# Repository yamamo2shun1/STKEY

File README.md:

# STKEY

C4NDY STK をベースにした、ジョイスティック付きキーボードの新プロジェクト。

## コンセプト

- キー配列は STK と同じ横10列 × 縦4行のオーソリニア
- ジョイスティックをメイン基板から分離し、親指の自然な向きに合わせて、手前＋中央方向へ傾けて設置する
- 中央にロータリーエンコーダーを 2×2 ブロックで4個搭載
- USB HID + MIDI の複合デバイス（オーディオ機能は搭載しない）
- MCU は STM32G491、ファームウェアは TinyUSB ベース。キーマップの書き換えは Confiseur で行う想定

## ドキュメント

- [仕様整理 v0.1](docs/spec-v0.1.md) — 決定事項と未決定事項の集約
- [回路設計スタートメモ](docs/circuit-design-start.md) — 現行STKのピン割り当てと新仕様での設計開始点

## ベースプロジェクト

- [C4NDY](https://github.com/yamamo2shun1/C4NDY) — STK / KeyVLM（STM32G491 + TinyUSB、USB Audio + HID）

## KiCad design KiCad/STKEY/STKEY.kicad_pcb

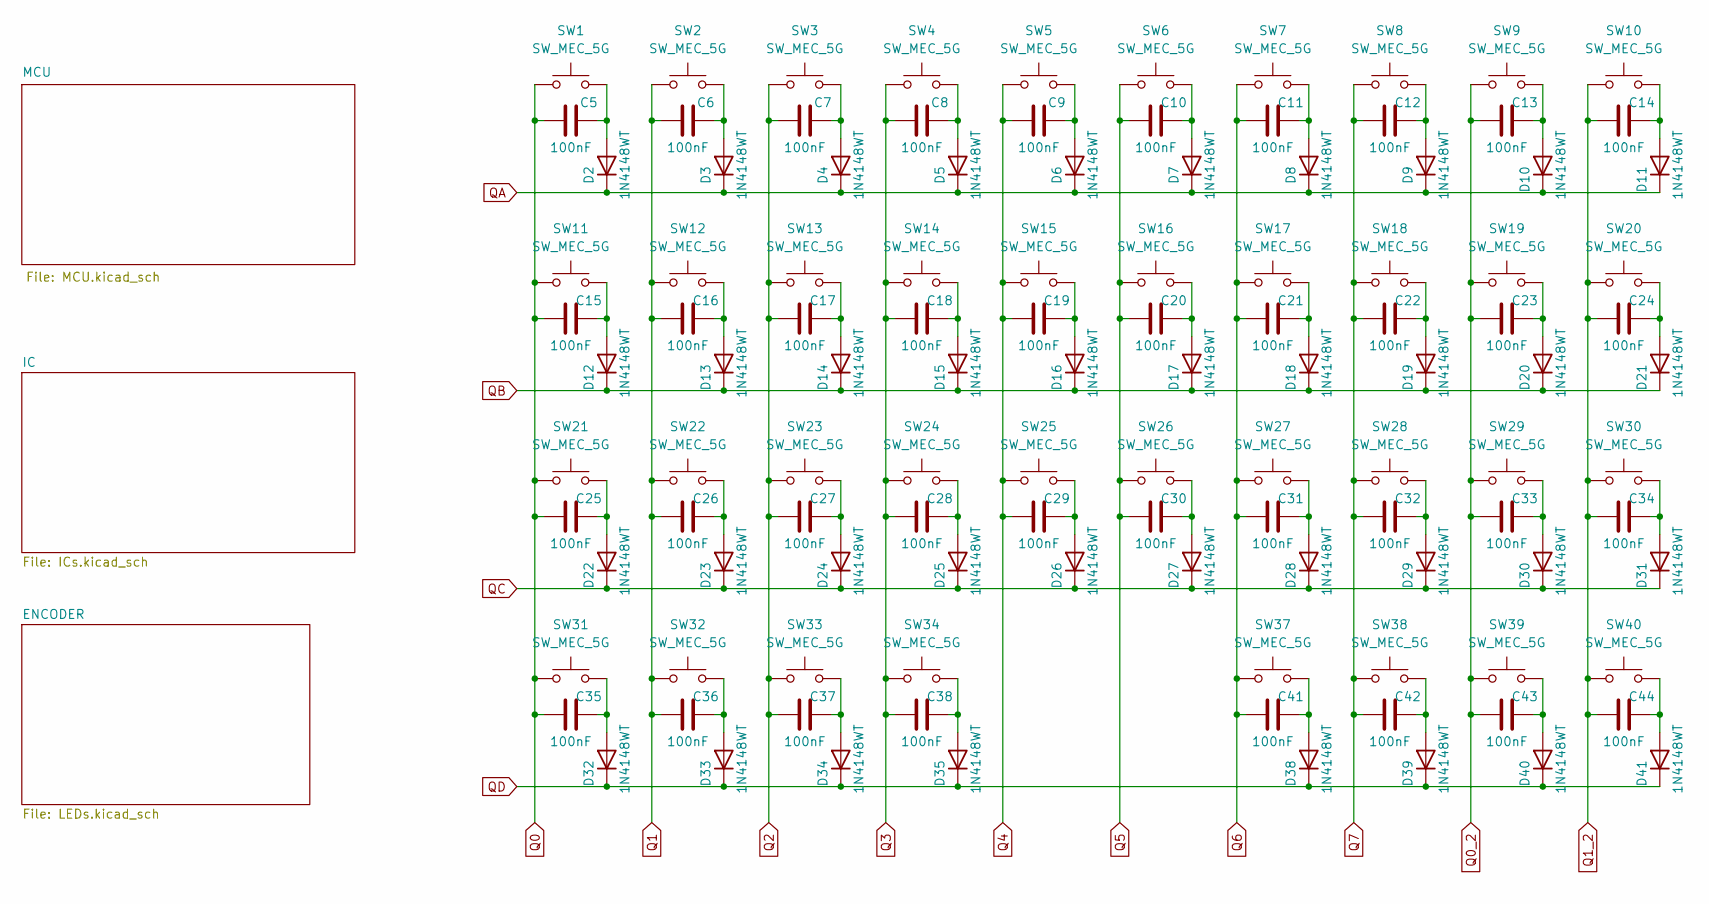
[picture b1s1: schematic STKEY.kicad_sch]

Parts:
C5, C6, C7, C8, C9, C10, C11, C12, C13, C14, C15, C16, C17, C18, C19, C20, C21, C22, C23, C24, C25, C26, C27, C28, C29, C30, C31, C32, C33, C34, C35, C36, C37, C38, C41, C42, C43, C44: 100nF; C_0402_1005Metric
D2, D3, D4, D5, D6, D7, D8, D9, D10, D11, D12, D13, D14, D15, D16, D17, D18, D19, D20, D21, D22, D23, D24, D25, D26, D27, D28, D29, D30, D31, D32, D33, D34, D35, D38, D39, D40, D41: 1N4148WT; D_SOD-523
SW1, SW2, SW3, SW4, SW5, SW6, SW7, SW8, SW9, SW10, SW11, SW12, SW13, SW14, SW15, SW16, SW17, SW18, SW19, SW20, SW21, SW22, SW23, SW24, SW25, SW26, SW27, SW28, SW29, SW30, SW31, SW32, SW33, SW34, SW37, SW38, SW39, SW40: SW_MEC_5G; Gateron_KS-27

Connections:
unnamed: C5.2, D2.2 (A), SW1.3 (B)
unnamed: C6.2, D3.2 (A), SW2.3 (B)
unnamed: C7.2, D4.2 (A), SW3.3 (B)
unnamed: C8.2, D5.2 (A), SW4.3 (B)
unnamed: C9.2, D6.2 (A), SW5.3 (B)
unnamed: C10.2, D7.2 (A), SW6.3 (B)
unnamed: C11.2, D8.2 (A), SW7.3 (B)
unnamed: C12.2, D9.2 (A), SW8.3 (B)
unnamed: C13.2, D10.2 (A), SW9.3 (B)
unnamed: C14.2, D11.2 (A), SW10.3 (B)
unnamed: C15.2, D12.2 (A), SW11.3 (B)
unnamed: C16.2, D13.2 (A), SW12.3 (B)
unnamed: C17.2, D14.2 (A), SW13.3 (B)
unnamed: C18.2, D15.2 (A), SW14.3 (B)
unnamed: C19.2, D16.2 (A), SW15.3 (B)
unnamed: C20.2, D17.2 (A), SW16.3 (B)
unnamed: C21.2, D18.2 (A), SW17.3 (B)
unnamed: C22.2, D19.2 (A), SW18.3 (B)
unnamed: C23.2, D20.2 (A), SW19.3 (B)
unnamed: C24.2, D21.2 (A), SW20.3 (B)
unnamed: C25.2, D22.2 (A), SW21.3 (B)
unnamed: C26.2, D23.2 (A), SW22.3 (B)
unnamed: C27.2, D24.2 (A), SW23.3 (B)
unnamed: C28.2, D25.2 (A), SW24.3 (B)
unnamed: C29.2, D26.2 (A), SW25.3 (B)
unnamed: C30.2, D27.2 (A), SW26.3 (B)
unnamed: C31.2, D28.2 (A), SW27.3 (B)
unnamed: C32.2, D29.2 (A), SW28.3 (B)
unnamed: C33.2, D30.2 (A), SW29.3 (B)
unnamed: C34.2, D31.2 (A), SW30.3 (B)
unnamed: C35.2, D32.2 (A), SW31.3 (B)
unnamed: C36.2, D33.2 (A), SW32.3 (B)
unnamed: C37.2, D34.2 (A), SW33.3 (B)
unnamed: C38.2, D35.2 (A), SW34.3 (B)
unnamed: C41.2, D38.2 (A), SW37.3 (B)
unnamed: C42.2, D39.2 (A), SW38.3 (B)
unnamed: C43.2, D40.2 (A), SW39.3 (B)
unnamed: C44.2, D41.2 (A), SW40.3 (B)
Q0: C5.1, C15.1, C25.1, C35.1, SW1.1 (A), SW11.1 (A), SW21.1 (A), SW31.1 (A); also elsewhere on the board
Q0_2: C13.1, C23.1, C33.1, C43.1, SW9.1 (A), SW19.1 (A), SW29.1 (A), SW39.1 (A); also elsewhere on the board
Q1: C6.1, C16.1, C26.1, C36.1, SW2.1 (A), SW12.1 (A), SW22.1 (A), SW32.1 (A); also elsewhere on the board
Q1_2: C14.1, C24.1, C34.1, C44.1, SW10.1 (A), SW20.1 (A), SW30.1 (A), SW40.1 (A); also elsewhere on the board
Q2: C7.1, C17.1, C27.1, C37.1, SW3.1 (A), SW13.1 (A), SW23.1 (A), SW33.1 (A); also elsewhere on the board
Q3: C8.1, C18.1, C28.1, C38.1, SW4.1 (A), SW14.1 (A), SW24.1 (A), SW34.1 (A); also elsewhere on the board
Q4: C9.1, C19.1, C29.1, SW5.1 (A), SW15.1 (A), SW25.1 (A); also elsewhere on the board
Q5: C10.1, C20.1, C30.1, SW6.1 (A), SW16.1 (A), SW26.1 (A); also elsewhere on the board
Q6: C11.1, C21.1, C31.1, C41.1, SW7.1 (A), SW17.1 (A), SW27.1 (A), SW37.1 (A); also elsewhere on the board
Q7: C12.1, C22.1, C32.1, C42.1, SW8.1 (A), SW18.1 (A), SW28.1 (A), SW38.1 (A); also elsewhere on the board
QA: D2.1 (K), D3.1 (K), D4.1 (K), D5.1 (K), D6.1 (K), D7.1 (K), D8.1 (K), D9.1 (K), D10.1 (K), D11.1 (K); also elsewhere on the board
QB: D12.1 (K), D13.1 (K), D14.1 (K), D15.1 (K), D16.1 (K), D17.1 (K), D18.1 (K), D19.1 (K), D20.1 (K), D21.1 (K); also elsewhere on the board
QC: D22.1 (K), D23.1 (K), D24.1 (K), D25.1 (K), D26.1 (K), D27.1 (K), D28.1 (K), D29.1 (K), D30.1 (K), D31.1 (K); also elsewhere on the board
QD: D32.1 (K), D33.1 (K), D34.1 (K), D35.1 (K), D38.1 (K), D39.1 (K), D40.1 (K), D41.1 (K); also elsewhere on the board

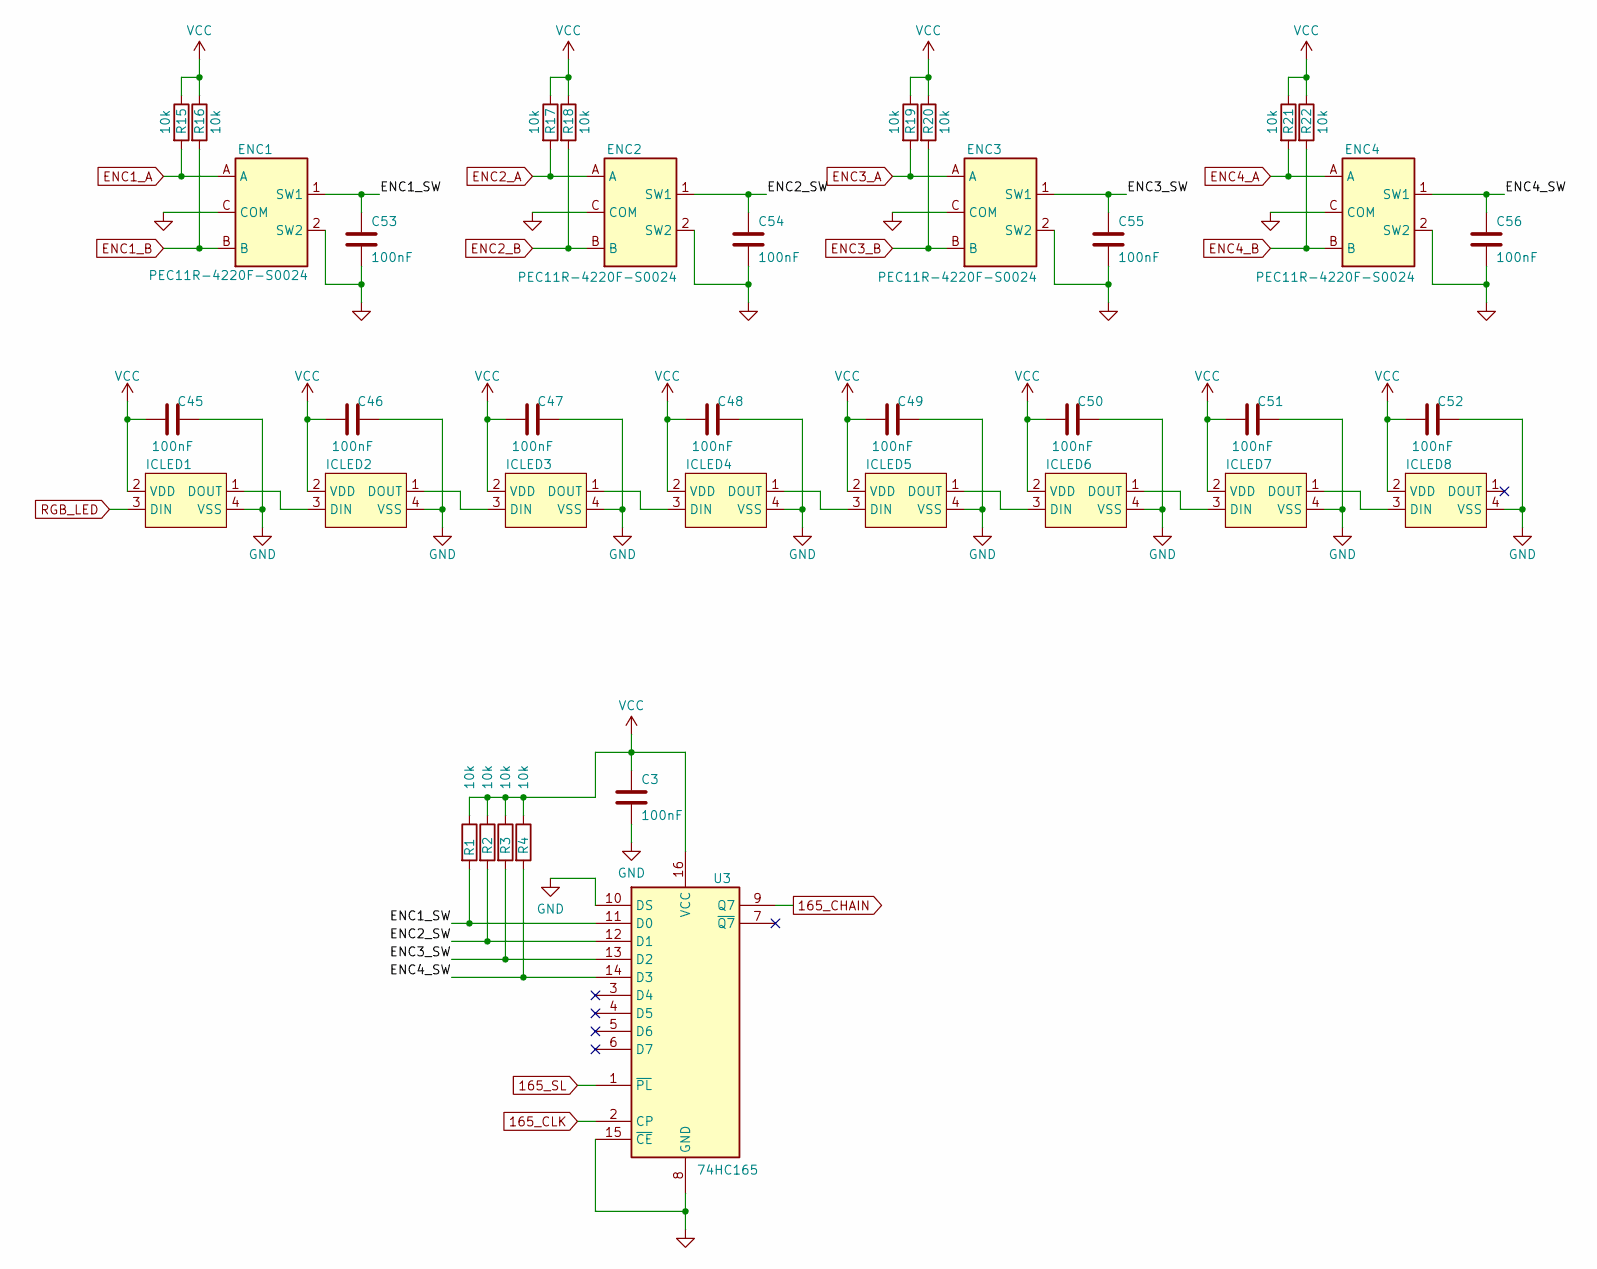
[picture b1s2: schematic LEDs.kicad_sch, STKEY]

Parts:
C3, C45, C46, C47, C48, C49, C50, C51, C52, C53, C54, C55, C56: 100nF; C_0402_1005Metric
ENC1, ENC2, ENC3, ENC4: PEC11R-4220F-S0024; XDCR_PEC11R-4220F-S0024
ICLED1, ICLED2, ICLED3, ICLED4, ICLED5, ICLED6, ICLED7, ICLED8: 1312020030000
R1, R2, R3, R4, R15, R16, R17, R18, R19, R20, R21, R22: 10k; R_0402_1005Metric
U3: 74HC165; SOIC-16_3.9x9.9mm_P1.27mm

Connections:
165_CHAIN: U3.9 (Q7); also elsewhere on the board
165_CLK: U3.2 (CP); also elsewhere on the board
165_SL: U3.1 (~PL); also elsewhere on the board
/ENCODER/ENC1_SW: C53.1, ENC1.1 (SW1), R1.2, U3.11 (D0)
/ENCODER/ENC2_SW: C54.1, ENC2.1 (SW1), R2.2, U3.12 (D1)
/ENCODER/ENC3_SW: C55.1, ENC3.1 (SW1), R3.2, U3.13 (D2)
/ENCODER/ENC4_SW: C56.1, ENC4.1 (SW1), R4.2, U3.14 (D3)
ENC1_A: ENC1.A, R15.2; also elsewhere on the board
ENC1_B: ENC1.B, R16.2; also elsewhere on the board
ENC2_A: ENC2.A, R17.2; also elsewhere on the board
ENC2_B: ENC2.B, R18.2; also elsewhere on the board
ENC3_A: ENC3.A, R19.2; also elsewhere on the board
ENC3_B: ENC3.B, R20.2; also elsewhere on the board
ENC4_A: ENC4.A, R21.2; also elsewhere on the board
ENC4_B: ENC4.B, R22.2; also elsewhere on the board
GND: C3.2, C45.2, C46.2, C47.2, C48.2, C49.2, C50.2, C51.2, C52.2, C53.2, C54.2, C55.2, C56.2, ENC1.2 (SW2), ENC1.C (COM), ENC2.2 (SW2), ENC2.C (COM), ENC3.2 (SW2), ENC3.C (COM), ENC4.2 (SW2), ENC4.C (COM), ICLED1.4 (VSS), ICLED2.4 (VSS), ICLED3.4 (VSS), ICLED4.4 (VSS), ICLED5.4 (VSS), ICLED6.4 (VSS), ICLED7.4 (VSS), ICLED8.4 (VSS), U3.8 (GND), U3.10 (DS), U3.15 (~CE); also elsewhere on the board
unnamed: ICLED1.1 (DOUT), ICLED2.3 (DIN)
unnamed: ICLED2.1 (DOUT), ICLED3.3 (DIN)
unnamed: ICLED3.1 (DOUT), ICLED4.3 (DIN)
unnamed: ICLED4.1 (DOUT), ICLED5.3 (DIN)
unnamed: ICLED5.1 (DOUT), ICLED6.3 (DIN)
unnamed: ICLED6.1 (DOUT), ICLED7.3 (DIN)
unnamed: ICLED7.1 (DOUT), ICLED8.3 (DIN)
RGB_LED: ICLED1.3 (DIN); also elsewhere on the board
VCC: C3.1, C45.1, C46.1, C47.1, C48.1, C49.1, C50.1, C51.1, C52.1, ICLED1.2 (VDD), ICLED2.2 (VDD), ICLED3.2 (VDD), ICLED4.2 (VDD), ICLED5.2 (VDD), ICLED6.2 (VDD), ICLED7.2 (VDD), ICLED8.2 (VDD), R1.1, R2.1, R3.1, R4.1, R15.1, R16.1, R17.1, R18.1, R19.1, R20.1, R21.1, R22.1, U3.16 (VCC); also elsewhere on the board

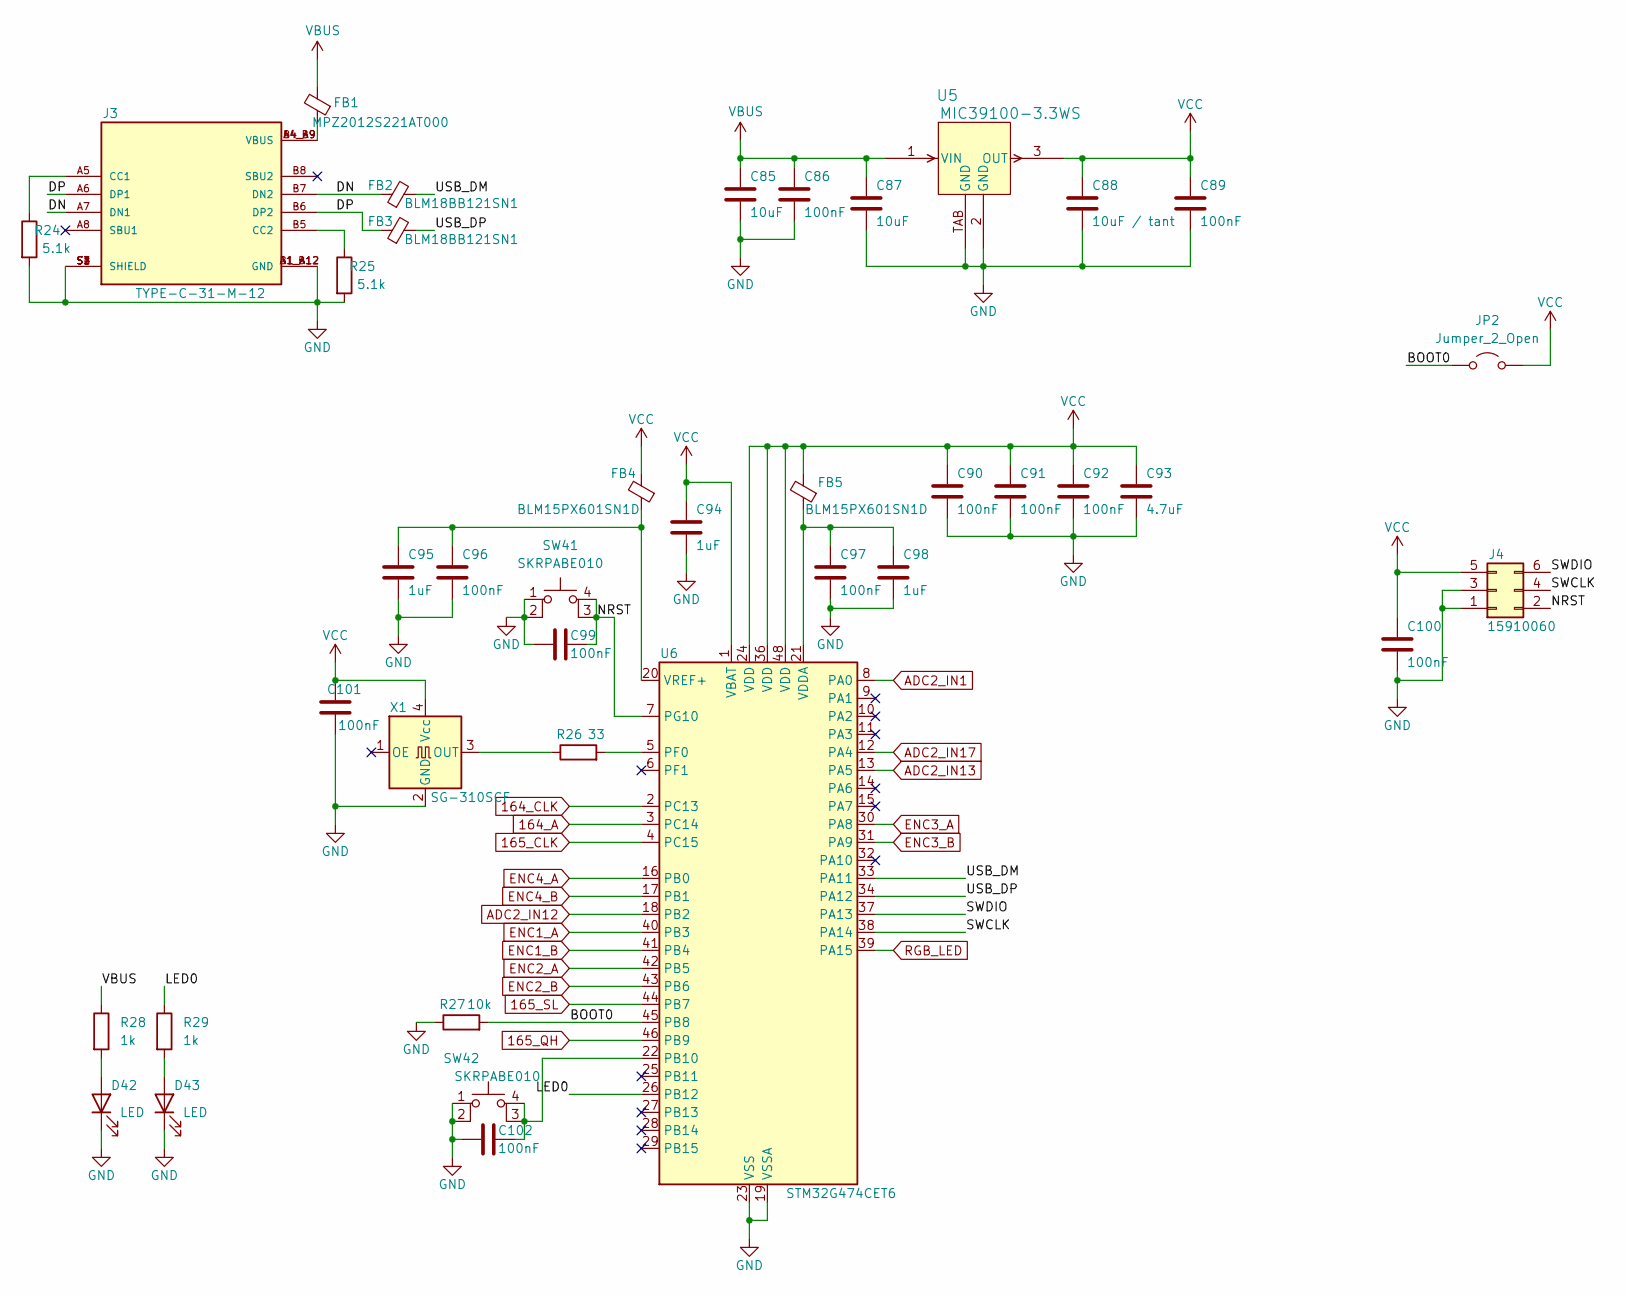
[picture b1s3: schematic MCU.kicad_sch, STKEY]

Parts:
C85, C87: 10uF; C_0603_1608Metric
C86, C89: 100nF; C_0603_1608Metric
C88: 10uF / tant; CP_EIA-3528-12_Kemet-T
C90, C91, C92, C96, C97, C99, C100, C101, C102: 100nF; C_0402_1005Metric
C93: 4.7uF; C_0603_1608Metric
C94, C95, C98: 1uF; C_0402_1005Metric
D42, D43: LED; LED_0603_1608Metric
FB1: MPZ2012S221AT000; L_0805_2012Metric
FB2, FB3: BLM18BB121SN1; L_0603_1608Metric
FB4, FB5: BLM15PX601SN1D; L_0402_1005Metric
J3: TYPE-C-31-M-12; Gangyuan_UB1611-HGN; PARTREV B
J4: 15910060; PinHeader_2x03_P2.54mm_Vertical
JP2: Jumper_2_Open; SolderJumper-2_P1.3mm_Open_RoundedPad1.0x1.5mm
R24, R25: 5.1k; R_0402_1005Metric
R26: 33; R_0402_1005Metric
R27: 10k; R_0402_1005Metric
R28, R29: 1k; R_0402_1005Metric
SW41, SW42: SKRPABE010
U5: MIC39100-3.3WS; SOT-223_S_MCL
U6: STM32G474CET6; LQFP-48_7x7mm_P0.5mm
X1: SG-310SCF; Oscillator_SMD_SeikoEpson_SG8002CE-4Pin_3.2x2.5mm

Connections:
164_A: U6.3 (PC14); also elsewhere on the board
164_CLK: U6.2 (PC13); also elsewhere on the board
165_CLK: U6.4 (PC15); also elsewhere on the board
165_QH: U6.46 (PB9); also elsewhere on the board
165_SL: U6.44 (PB7); also elsewhere on the board
/MCU/BOOT0: JP2.1 (A), R27.2, U6.45 (PB8)
/MCU/DN: FB2.1, J3.A7 (DN1), J3.B7 (DN2)
/MCU/DP: FB3.1, J3.A6 (DP1), J3.B6 (DP2)
/MCU/LED0: R29.1, U6.26 (PB12)
/MCU/NRST: C99.1, J4.2, SW41.3 (K), SW41.4 (A), U6.7 (PG10)
/MCU/SWCLK: J4.4, U6.38 (PA14)
/MCU/SWDIO: J4.6, U6.37 (PA13)
/MCU/USB_DM: FB2.2, U6.33 (PA11)
/MCU/USB_DP: FB3.2, U6.34 (PA12)
ADC2_IN1: U6.8 (PA0); also elsewhere on the board
ADC2_IN12: U6.18 (PB2); also elsewhere on the board
ADC2_IN13: U6.13 (PA5); also elsewhere on the board
ADC2_IN17: U6.12 (PA4); also elsewhere on the board
ENC1_A: U6.40 (PB3); also elsewhere on the board
ENC1_B: U6.41 (PB4); also elsewhere on the board
ENC2_A: U6.42 (PB5); also elsewhere on the board
ENC2_B: U6.43 (PB6); also elsewhere on the board
ENC3_A: U6.30 (PA8); also elsewhere on the board
ENC3_B: U6.31 (PA9); also elsewhere on the board
ENC4_A: U6.16 (PB0); also elsewhere on the board
ENC4_B: U6.17 (PB1); also elsewhere on the board
GND: C85.2, C86.2, C87.2, C88.2, C89.2, C90.2, C91.2, C92.2, C93.2, C94.2, C95.2, C96.2, C97.2, C98.2, C99.2, C100.2, C101.1, C102.2, D42.1 (K), D43.1 (K), J3.A1_B12 (GND), J3.B1_A12 (GND), J3.S1 (SHIELD), J3.S2 (SHIELD), J3.S3 (SHIELD), J3.S4 (SHIELD), J4.1, J4.3, R24.2, R25.2, R27.1, SW41.1, SW41.2, SW42.1, SW42.2, U5.2 (GND), U5.TAB (GND), U6.19 (VSSA), U6.23 (VSS), U6.35 (VSS), U6.47 (VSS), X1.2 (GND); also elsewhere on the board
unnamed: D42.2 (A), R28.2
unnamed: D43.2 (A), R29.2
unnamed: FB1.1, J3.A4_B9 (VBUS), J3.B4_A9 (VBUS)
unnamed: J3.A5 (CC1), R24.1
unnamed: J3.B5 (CC2), R25.1
unnamed: C102.1, SW42.3 (K), SW42.4 (A), U6.22 (PB10)
unnamed: R26.2, U6.5 (PF0)
unnamed: C97.1, C98.1, FB5.1, U6.21 (VDDA)
unnamed: C95.1, C96.1, FB4.1, U6.20 (VREF+)
unnamed: R26.1, X1.3 (OUT)
RGB_LED: U6.39 (PA15); also elsewhere on the board
VBUS: C85.1, C86.1, C87.1, FB1.2, R28.1, U5.1 (VIN)
VCC: C88.1, C89.1, C90.1, C91.1, C92.1, C93.1, C94.1, C100.1, C101.2, FB4.2, FB5.2, J4.5, JP2.2 (B), U5.3 (OUT), U6.1 (VBAT), U6.24 (VDD), U6.36 (VDD), U6.48 (VDD), X1.4 (Vcc); also elsewhere on the board

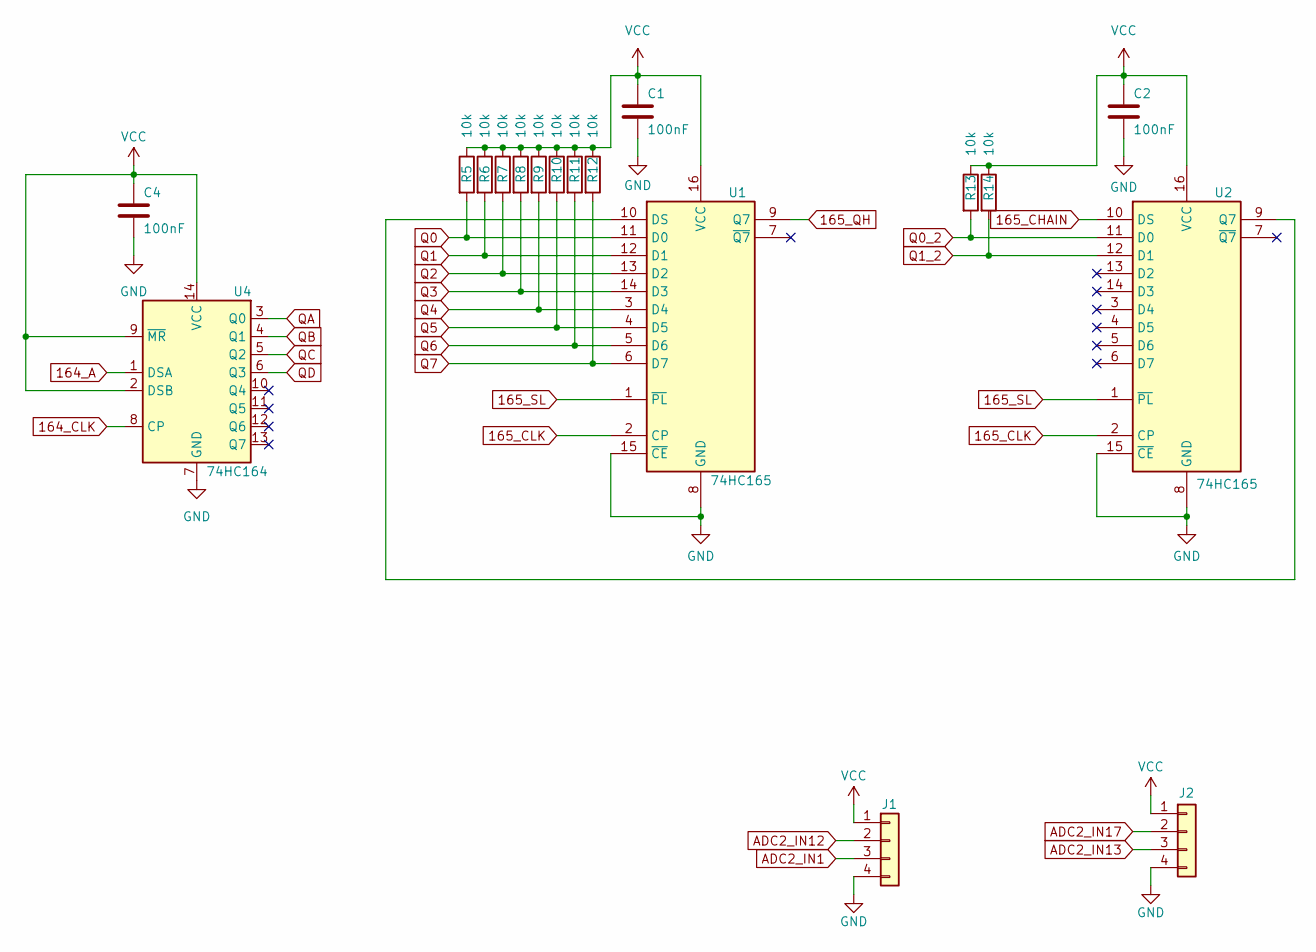
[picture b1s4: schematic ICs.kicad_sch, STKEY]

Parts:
C1, C2, C4: 100nF; C_0402_1005Metric
J1, J2: Conn_01x04; JST_SH_SM04B-SRSS-TB_1x04-1MP_P1.00mm_Horizontal
R5, R6, R7, R8, R9, R10, R11, R12, R13, R14: 10k; R_0402_1005Metric
U1, U2: 74HC165; SOIC-16_3.9x9.9mm_P1.27mm
U4: 74HC164; SOIC-14_3.9x8.7mm_P1.27mm

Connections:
164_A: U4.1 (DSA); also elsewhere on the board
164_CLK: U4.8 (CP); also elsewhere on the board
165_CHAIN: U2.10 (DS); also elsewhere on the board
165_CLK: U1.2 (CP), U2.2 (CP); also elsewhere on the board
165_QH: U1.9 (Q7); also elsewhere on the board
165_SL: U1.1 (~PL), U2.1 (~PL); also elsewhere on the board
ADC2_IN1: J1.3; also elsewhere on the board
ADC2_IN12: J1.2; also elsewhere on the board
ADC2_IN13: J2.3; also elsewhere on the board
ADC2_IN17: J2.2; also elsewhere on the board
GND: C1.2, C2.2, C4.2, J1.4, J2.4, U1.8 (GND), U1.15 (~CE), U2.8 (GND), U2.15 (~CE), U4.7 (GND); also elsewhere on the board
unnamed: U1.10 (DS), U2.9 (Q7)
Q0: R5.2, U1.11 (D0); also elsewhere on the board
Q0_2: R13.2, U2.11 (D0); also elsewhere on the board
Q1: R6.2, U1.12 (D1); also elsewhere on the board
Q1_2: R14.2, U2.12 (D1); also elsewhere on the board
Q2: R7.2, U1.13 (D2); also elsewhere on the board
Q3: R8.2, U1.14 (D3); also elsewhere on the board
Q4: R9.2, U1.3 (D4); also elsewhere on the board
Q5: R10.2, U1.4 (D5); also elsewhere on the board
Q6: R11.2, U1.5 (D6); also elsewhere on the board
Q7: R12.2, U1.6 (D7); also elsewhere on the board
QA: U4.3 (Q0); also elsewhere on the board
QB: U4.4 (Q1); also elsewhere on the board
QC: U4.5 (Q2); also elsewhere on the board
QD: U4.6 (Q3); also elsewhere on the board
VCC: C1.1, C2.1, C4.1, J1.1, J2.1, R5.1, R6.1, R7.1, R8.1, R9.1, R10.1, R11.1, R12.1, R13.1, R14.1, U1.16 (VCC), U2.16 (VCC), U4.2 (DSB), U4.9 (~MR), U4.14 (VCC); also elsewhere on the board

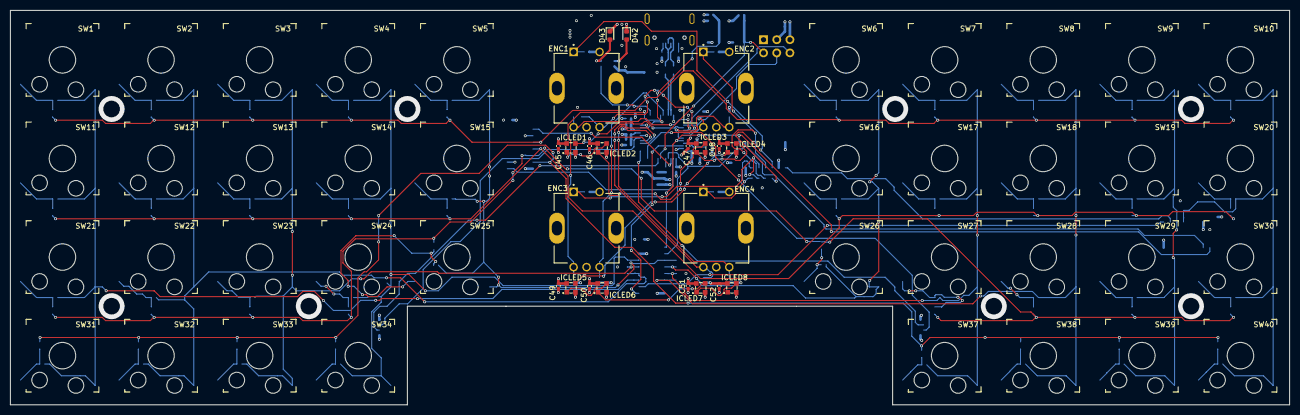
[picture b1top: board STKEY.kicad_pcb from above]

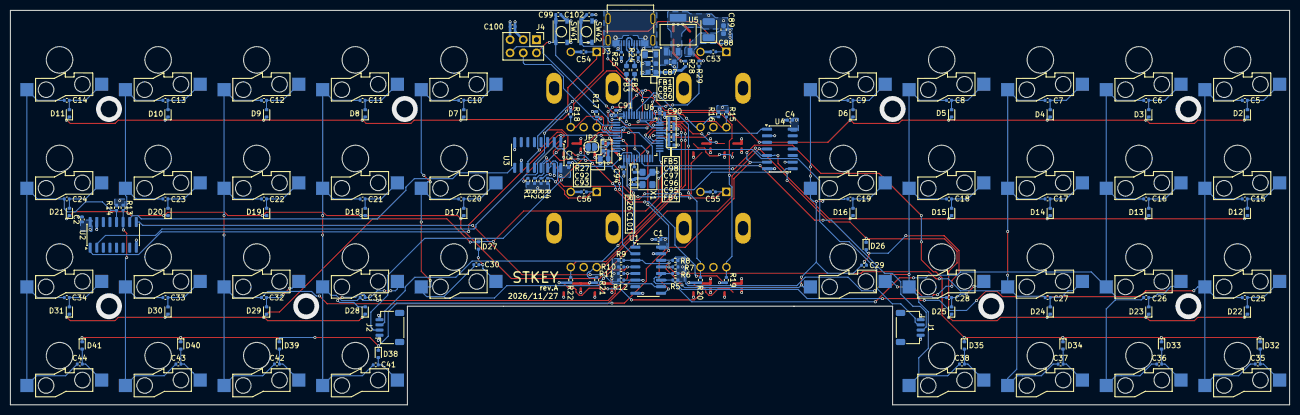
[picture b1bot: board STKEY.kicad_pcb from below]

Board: 4 copper layers, 246.5 x 76.0 mm, 209 parts (187 on the bottom side), 105 nets.
